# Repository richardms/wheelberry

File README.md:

# wheelberry
Electric wheelchair based Raspberry Pi projects

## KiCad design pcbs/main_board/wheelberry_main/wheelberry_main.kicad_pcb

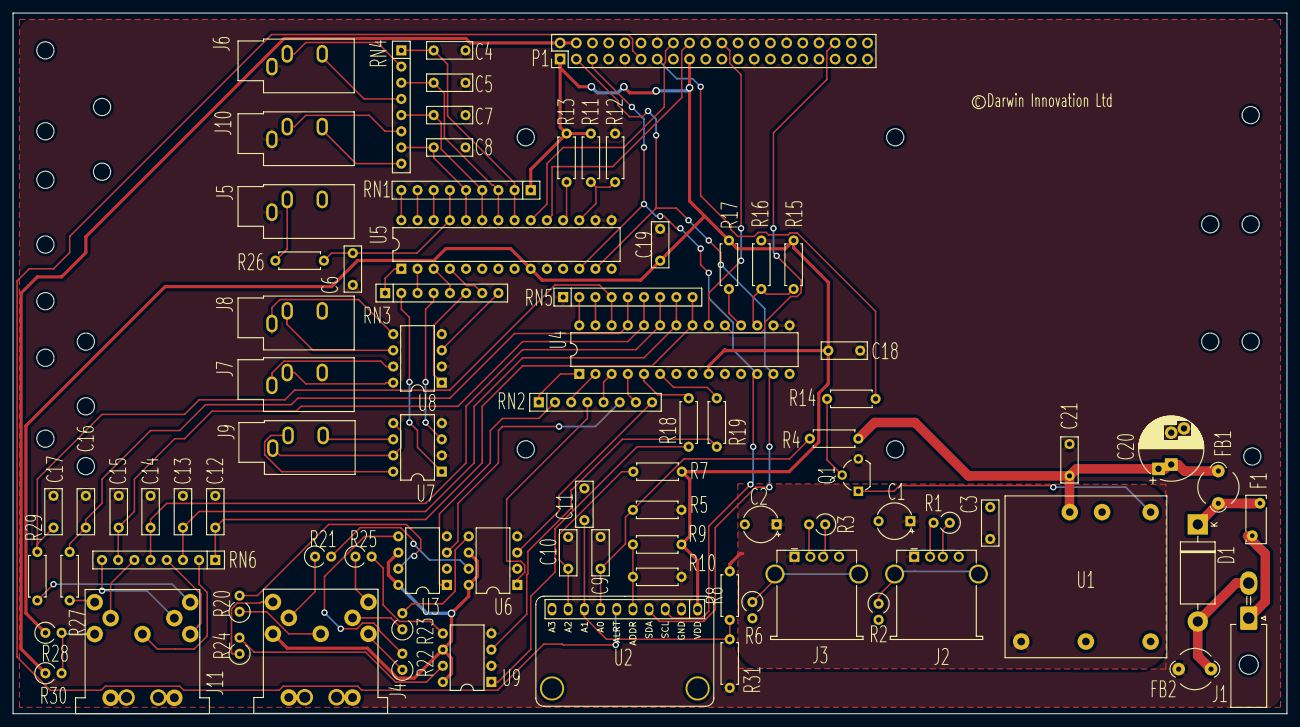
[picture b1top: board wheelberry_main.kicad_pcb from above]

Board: 2 copper layers, 200.0 x 110.0 mm, 106 parts (0 on the bottom side), 100 nets.

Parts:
C1, C2: 47u; CP_Radial_Tantal_D5.5mm_P5.00mm
C3, C4, C5, C6, C7, C8, C9, C10, C11, C12, C13, C14, C15, C16, C17, C18, C19, C21: 100n; C_Rect_L7.0mm_W2.5mm_P5.00mm
C20: 10u; CP_Radial_D10.0mm_P5.00mm_P7.50mm
D1: 1N5400; D_DO-201AD_P15.24mm_Horizontal
F1: Polyfuse_Small; Fuse_Bourns_MF-RHT050
FB1, FB2: Ferrite_Bead_Small; LairdTech_28C0236-0JW-10
J1: Conn_01x02_Male; Molex_Mini-Fit_Jr_5569-02A2_2x01_P4.20mm_Horizontal
J2, J3: USB_A; USB_A_Stewart_SS-52100-001_Horizontal
J4, J11: DIN-7; pro-signal_DIN7_Socket
J5, J7, J8: AudioJack2; Jack_3.5mm_CUI_SJ1-3533NG_Horizontal
J6, J9, J10: AudioJack3; Jack_3.5mm_CUI_SJ1-3533NG_Horizontal
MK1, MK2, MK3, MK4, MK5, MK6, MK7, MK8, MK9, MK10, MK11, MK12, MK13, MK14, MK15, MK16, MK17, MK18, MK19, MK20, MK21, MK22: M2.5; MountingHole_2.7mm_M2.5
P1: Conn_02x20_Odd_Even; PinHeader_2x20_P2.54mm_Vertical
Q1: Q_NMOS_DGS; TO-92_Wide
R1, R2, R3, R6: 47; R_Axial_DIN0309_L9.0mm_D3.2mm_P2.54mm_Vertical
R4: 100k; R_Axial_DIN0207_L6.3mm_D2.5mm_P7.62mm_Horizontal
R5, R8, R11, R12, R13, R15, R16, R17, R31: 10k; R_Axial_DIN0207_L6.3mm_D2.5mm_P7.62mm_Horizontal
R7, R14: 100; R_Axial_DIN0207_L6.3mm_D2.5mm_P7.62mm_Horizontal
R9, R10: 4k7; R_Axial_DIN0207_L6.3mm_D2.5mm_P7.62mm_Horizontal
R18, R19: 330; R_Axial_DIN0207_L6.3mm_D2.5mm_P7.62mm_Horizontal
R20, R21, R22, R23, R24, R25, R28, R30: 10; R_Axial_DIN0309_L9.0mm_D3.2mm_P2.54mm_Vertical
R26, R27, R29: 1k; R_Axial_DIN0207_L6.3mm_D2.5mm_P7.62mm_Horizontal
RN1, RN5: 10k; R_Array_SIP9
RN2, RN3: 330; R_Array_SIP8
RN4, RN6: 1k; R_Array_SIP8
U1: THN_15-2411; Traco_THN15
U2: ADS1115IDGS; Adafruit_ADS1x15_Breakout
U3, U6, U7, U8, U9: TLP222A-2; DIP-8_W7.62mm
U4, U5: MCP23017_SO; DIP-28_W7.62mm

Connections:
+3V3: C18.1, C19.1, P1.1, P1.17, R7.2, R9.1, R11.1, R13.1, R15.1, R17.1, R28.1, RN1.1, U2.8, U4.9, U5.9
+5V: P1.2, P1.4, R30.1
+5VP: C1.1, C2.1, C3.1, J2.1, J3.1, R8.2, U1.3
/24V_IN+: F1.2, J1.1
/24V_IN-: D1.2, FB2.2, J1.2
/EXP_INTA: P1.16, U5.20
/EXP_INTB: P1.18, U5.19
/GPIO2(SDA1): P1.3, U2.9, U4.13, U5.13
/GPIO3(SCL1): P1.5, U2.10, U4.12, U5.12
/GPIO16: P1.36, U4.19
/GPIO17(GEN0): P1.11, U2.2
/GPIO25(GEN6): P1.22, U4.20
/GPIO27(GEN2): P1.13, R14.2
/Wheelberry IO/GPB0: RN3.1, U5.1
/Wheelberry IO/GPB1: RN3.3, U5.2
/Wheelberry IO/GPB2: RN3.5, U5.3
/Wheelberry IO/GPB3: RN3.7, U5.4
/Wheelberry Power/24V_IN: C20.1, C21.1, FB1.1, R4.1, U1.1
/Wheelberry Power/24V_MEAS: C9.1, R4.2, R5.1, U2.4
/Wheelchair IO Bed/GPB0: RN2.1, U4.1
/Wheelchair IO Bed/GPB1: RN2.3, U4.2
/Wheelchair IO Bed/GPB2: RN2.5, U4.3
/Wheelchair IO Bed/GPB3: RN2.7, U4.4
/Wheelchair IO Bed/GPB4: R18.2, U4.5
/Wheelchair IO Bed/GPB5: R19.2, U4.6
GND: C1.2, C2.2, C3.2, C4.2, C5.2, C6.2, C7.2, C8.2, C9.2, C10.2, C11.2, C12.2, C13.2, C14.2, C15.2, C16.2, C17.2, C18.2, C19.2, C20.2, C21.2, FB2.1, J2.4, J3.4, J5.S, J6.S, J10.S, P1.6, P1.9, P1.14, P1.20, P1.25, P1.30, P1.34, P1.39, Q1.3, R2.2, R5.2, R6.2, R10.2, R12.2, R16.2, R31.1, RN5.1, U1.2, U1.5, U2.3, U3.2, U3.4, U4.10, U4.15, U4.16, U5.10, U5.15, U5.16, U6.2, U6.4, U7.2, U7.4, U8.2, U8.4, U9.2, U9.4
unnamed: C4.1, RN1.2, RN4.1, U5.21
unnamed: C5.1, RN1.3, RN4.3, U5.22
unnamed: C6.1, R26.2, RN1.6, U5.25
unnamed: C7.1, RN1.4, RN4.5, U5.23
unnamed: C8.1, RN1.5, RN4.7, U5.24
unnamed: C10.1, R7.1, U2.6
unnamed: C11.1, R8.1, R31.2, U2.5
unnamed: C12.1, RN5.9, RN6.1, U4.21
unnamed: C13.1, RN5.8, RN6.3, U4.22
unnamed: C14.1, RN5.7, RN6.5, U4.23
unnamed: C15.1, RN5.6, RN6.7, U4.24
unnamed: C16.1, R27.2, RN5.5, U4.25
unnamed: C17.1, R29.2, RN5.4, U4.26
unnamed: D1.1, F1.1, FB1.2
unnamed: J2.2, R1.2
unnamed: J2.3, R1.1
unnamed: J2.5, R2.1
unnamed: J3.2, R3.2
unnamed: J3.3, R3.1
unnamed: J3.5, R6.1
unnamed: J4.1, U3.6, U3.8, U6.6, U6.8, U9.6, U9.8
unnamed: J4.2, R20.1
unnamed: J4.3, R22.1
unnamed: J4.4, R21.1
unnamed: J4.5, R23.1
unnamed: J4.6, R24.1
unnamed: J4.7, R25.1
unnamed: J5.T, R26.1
unnamed: J6.R, RN4.4
unnamed: J6.T, RN4.2
unnamed: J7.S, U8.7
unnamed: J7.T, U8.8
unnamed: J8.S, U8.5
unnamed: J8.T, U8.6
unnamed: J9.R, U7.6
unnamed: J9.S, U7.5, U7.7
unnamed: J9.T, U7.8
unnamed: J10.R, RN4.8
unnamed: J10.T, RN4.6
unnamed: J11.1, R28.2, R30.2
unnamed: J11.2, RN6.2
unnamed: J11.3, RN6.4
unnamed: J11.4, RN6.6
unnamed: J11.5, RN6.8
unnamed: J11.6, R27.1
unnamed: J11.7, R29.1
unnamed: Q1.1, U1.6
unnamed: Q1.2, R14.1
unnamed: R9.2, R10.1, U2.1
unnamed: R11.2, R12.1, U5.17
unnamed: R13.2, U5.18
unnamed: R15.2, R16.1, U4.17
unnamed: R17.2, U4.18
unnamed: R18.1, U9.1
unnamed: R19.1, U9.3
unnamed: R20.2, U3.7
unnamed: R21.2, U6.7
unnamed: R22.2, U3.5
unnamed: R23.2, U6.5
unnamed: R24.2, U9.7
unnamed: R25.2, U9.5
unnamed: RN1.7, U5.26
unnamed: RN1.8, U5.27
unnamed: RN1.9, U5.28
unnamed: RN2.2, U3.1
unnamed: RN2.4, U6.1
unnamed: RN2.6, U3.3
unnamed: RN2.8, U6.3
unnamed: RN3.2, U7.1
unnamed: RN3.4, U7.3
unnamed: RN3.6, U8.1
unnamed: RN3.8, U8.3
unnamed: RN5.2, U4.28
unnamed: RN5.3, U4.27

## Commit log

2020-01-04 Import
2020-01-21 Add bedside sw
2020-01-27 v1.2
2020-01-30 add 1st sw version
2020-01-31 example system rev 1
2020-02-04 switch to onoff for interrupts
2020-02-04 remove debugging
2020-02-04 wait for intent on launch
2020-02-04 update presets
2020-02-20 rotate acc'r
2020-03-15 Bump acorn from 7.1.0 to 7.1.1 in /software/bedside
    Bumps [acorn](https://github.com/acornjs/acorn) from 7.1.0 to 7.1.1.
    - [Release notes](https://github.com/acornjs/acorn/releases)
    - [Commits](https://github.com/acornjs/acorn/compare/7.1.0...7.1.1)
2020-07-19 Bump lodash from 4.17.15 to 4.17.19 in /software/bedside
    Bumps [lodash](https://github.com/lodash/lodash) from 4.17.15 to 4.17.19.
    - [Release notes](https://github.com/lodash/lodash/releases)
    - [Commits](https://github.com/lodash/lodash/compare/4.17.15...4.17.19)
2020-12-12 Bump ini from 1.3.5 to 1.3.8 in /software/bedside
    Bumps [ini](https://github.com/isaacs/ini) from 1.3.5 to 1.3.8.
    - [Release notes](https://github.com/isaacs/ini/releases)
    - [Commits](https://github.com/isaacs/ini/compare/v1.3.5...v1.3.8)
2021-03-31 Bump y18n from 4.0.0 to 4.0.1 in /software/bedside
    Bumps [y18n](https://github.com/yargs/y18n) from 4.0.0 to 4.0.1.
    - [Release notes](https://github.com/yargs/y18n/releases)
    - [Changelog](https://github.com/yargs/y18n/blob/master/CHANGELOG.md)
    - [Commits](https://github.com/yargs/y18n/commits)
2021-05-11 Bump lodash from 4.17.15 to 4.17.21 in /software/bedside
    Bumps [lodash](https://github.com/lodash/lodash) from 4.17.15 to 4.17.21.
    - [Release notes](https://github.com/lodash/lodash/releases)
    - [Commits](https://github.com/lodash/lodash/compare/4.17.15...4.17.21)
2021-05-11 Bump acorn from 7.1.0 to 7.4.1 in /software/bedside
    Bumps [acorn](https://github.com/acornjs/acorn) from 7.1.0 to 7.4.1.
    - [Release notes](https://github.com/acornjs/acorn/releases)
    - [Commits](https://github.com/acornjs/acorn/compare/7.1.0...7.4.1)
2021-05-11 Bump dot-prop from 4.2.0 to 4.2.1 in /software/bedside
    Bumps [dot-prop](https://github.com/sindresorhus/dot-prop) from 4.2.0 to 4.2.1.
    - [Release notes](https://github.com/sindresorhus/dot-prop/releases)
    - [Commits](https://github.com/sindresorhus/dot-prop/compare/v4.2.0...v4.2.1)
2021-08-11 Bump path-parse from 1.0.6 to 1.0.7 in /software/bedside
    Bumps [path-parse](https://github.com/jbgutierrez/path-parse) from 1.0.6 to 1.0.7.
    - [Release notes](https://github.com/jbgutierrez/path-parse/releases)
    - [Commits](https://github.com/jbgutierrez/path-parse/commits/v1.0.7)
    ---
    updated-dependencies:
    - dependency-name: path-parse
2021-10-08 abstract logger
2021-10-08 abstract logger 2
2021-10-08 format
2021-10-08 update test
2021-10-08 compile all source
2021-10-08 pre-compile on dev
2021-10-11 Add Multi-button
2021-10-11 multibutton test app
2021-10-20 Allow bit setting
2021-12-17 import configuration
2021-12-17 update config
2021-12-19 fix compilation
2021-12-19 Add extral support
2022-01-15 Bump shelljs from 0.8.4 to 0.8.5 in /software/bedside
    Bumps [shelljs](https://github.com/shelljs/shelljs) from 0.8.4 to 0.8.5.
    - [Release notes](https://github.com/shelljs/shelljs/releases)
    - [Changelog](https://github.com/shelljs/shelljs/blob/master/CHANGELOG.md)
    - [Commits](https://github.com/shelljs/shelljs/compare/v0.8.4...v0.8.5)
    ---
    updated-dependencies:
2022-12-05 Bump decode-uri-component from 0.2.0 to 0.2.2 in /software/bedside
    Bumps [decode-uri-component](https://github.com/SamVerschueren/decode-uri-component) from 0.2.0 to 0.2.2.
    - [Release notes](https://github.com/SamVerschueren/decode-uri-component/releases)
    - [Commits](https://github.com/SamVerschueren/decode-uri-component/compare/v0.2.0...v0.2.2)
    ---
    updated-dependencies:
    - dependency-name: decode-uri-component
2022-12-07 Bump qs, body-parser and express in /software/bedside
    Bumps [qs](https://github.com/ljharb/qs) to 6.11.0 and updates ancestor dependencies [qs](https://github.com/ljharb/qs), [body-parser](https://github.com/expressjs/body-parser) and [express](https://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
    Updates `qs` from 6.9.6 to 6.11.0
    - [Release notes](https://github.com/ljharb/qs/releases)
    - [Changelog](https://github.com/ljharb/qs/blob/main/CHANGELOG.md)
    - [Commits](https://github.com/ljharb/qs/compare/v6.9.6...v6.11.0)
    Updates `body-parser` from 1.19.1 to 1.20.1
2022-12-15 Bump express from 4.17.2 to 4.17.3 in /software/bedside
    Bumps [express](https://github.com/expressjs/express) from 4.17.2 to 4.17.3.
    - [Release notes](https://github.com/expressjs/express/releases)
    - [Changelog](https://github.com/expressjs/express/blob/master/History.md)
    - [Commits](https://github.com/expressjs/express/compare/4.17.2...4.17.3)
    ---
    updated-dependencies:
2022-12-30 Bump flat and mocha in /software/bedside
    Bumps [flat](https://github.com/hughsk/flat) to 5.0.2 and updates ancestor dependency [mocha](https://github.com/mochajs/mocha). These dependencies need to be updated together.
    Updates `flat` from 4.1.1 to 5.0.2
    - [Release notes](https://github.com/hughsk/flat/releases)
    - [Commits](https://github.com/hughsk/flat/compare/4.1.1...5.0.2)
    Updates `mocha` from 6.2.3 to 10.2.0
    - [Release notes](https://github.com/mochajs/mocha/releases)
2023-01-07 Bump json5 from 2.2.0 to 2.2.2 in /software/bedside
    Bumps [json5](https://github.com/json5/json5) from 2.2.0 to 2.2.2.
    - [Release notes](https://github.com/json5/json5/releases)
    - [Changelog](https://github.com/json5/json5/blob/main/CHANGELOG.md)
    - [Commits](https://github.com/json5/json5/compare/v2.2.0...v2.2.2)
    ---
    updated-dependencies:
2023-01-24 Bump cookiejar from 2.1.3 to 2.1.4 in /software/bedside
    Bumps [cookiejar](https://github.com/bmeck/node-cookiejar) from 2.1.3 to 2.1.4.
    - [Release notes](https://github.com/bmeck/node-cookiejar/releases)
    - [Commits](https://github.com/bmeck/node-cookiejar/commits)
    ---
    updated-dependencies:
    - dependency-name: cookiejar
2026-01-03 Bump qs, body-parser and express in /software/bedside
    Bumps [qs](https://github.com/ljharb/qs) to 6.14.1 and updates ancestor dependencies [qs](https://github.com/ljharb/qs), [body-parser](https://github.com/expressjs/body-parser) and [express](https://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
    Updates `qs` from 6.9.6 to 6.14.1
    - [Changelog](https://github.com/ljharb/qs/blob/main/CHANGELOG.md)
    - [Commits](https://github.com/ljharb/qs/compare/v6.9.6...v6.14.1)
    Updates `body-parser` from 1.19.1 to 1.20.4
    - [Release notes](https://github.com/expressjs/body-parser/releases)
